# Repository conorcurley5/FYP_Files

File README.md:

# FYP Portfolio Supplementary Files

Due to the quantity of code involved in this project, all files are stored in this GitHub repository. There's almost 1GB of data here, so the portfolio would end up being significantly more than 100 pages.

# Folders

There are four folders in this project:

 - CCS Application
 - KiCAD
 - SolidWorks
 - User Interface Application

## CCS Application

This folder holds the code for the PlatformIO-based CCS software. The primary folder in here is "(Main)FYP Project - ESP", however older revisions of the software, and revisions for different platforms, are available also.

## KiCAD

This folder holds all of the PCB designs for the project, including multiple revisions of the heater, and an unused design for a motor controller board.

## SolidWorks

This folder holds all of the 3D models for the project, as well as some renders used in the portfolio.

- Assemblies holds packaged assemblies for the project. RigV2 is the version used in the portfolio.
- Renders holds the renders used in the report.
- All files holds every revision of every file in the project, but these aren't packed to go.

## User Interface Application

This folder holds the front-end application for the project, build with NextJS. There is only one version of this application. You'll need NodeJS installed to run these.

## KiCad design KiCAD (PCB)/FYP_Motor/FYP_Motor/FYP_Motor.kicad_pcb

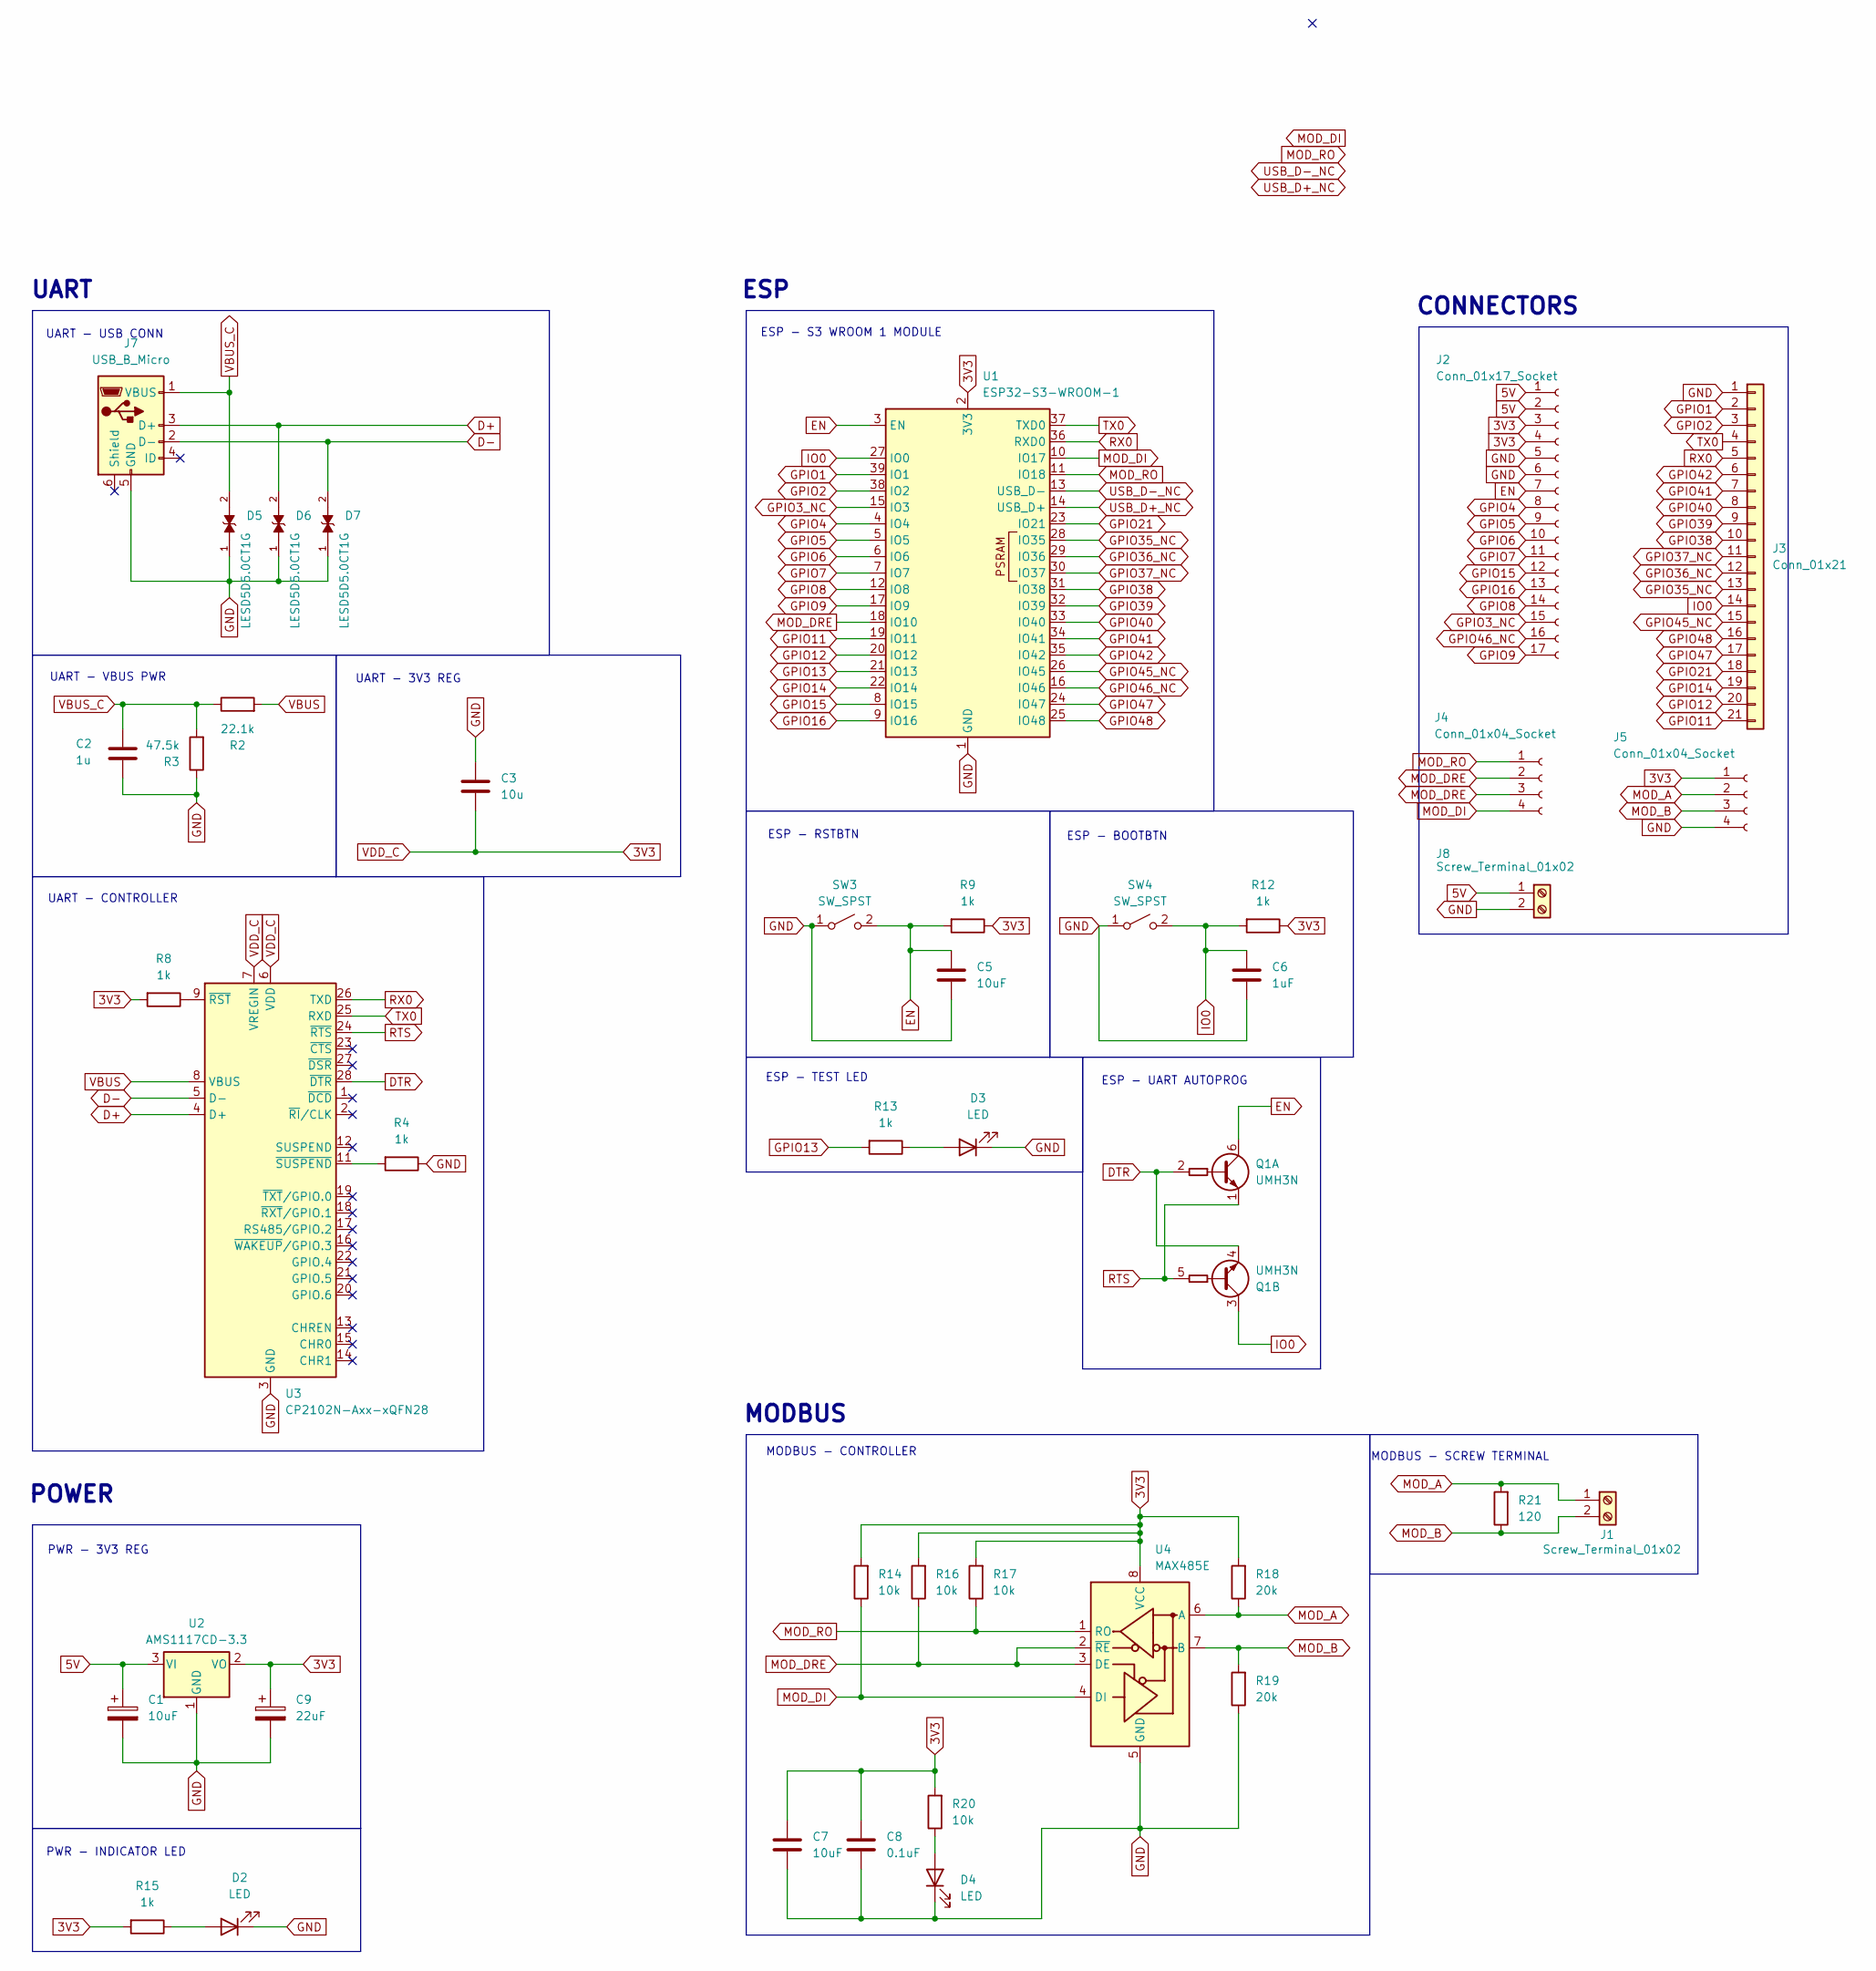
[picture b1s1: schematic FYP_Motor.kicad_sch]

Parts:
C1: 10uF; CP_EIA-3216-18_Kemet-A
C2: 1u; C_0402_1005Metric
C3: 10u; C_0603_1608Metric
C5, C7: 10uF; C_0603_1608Metric
C6: 1uF; C_0402_1005Metric
C8: 0.1uF; C_0402_1005Metric
C9: 22uF; CP_EIA-3216-18_Kemet-A
D2, D3, D4: LED; LED_0603_1608Metric
D5, D6, D7: LESD5D5.0CT1G; TVS_LESD5D5.0CT1G; PARTREV O
J1, J8: Screw_Terminal_01x02; TerminalBlock_Altech_AK300-2_P5.00mm
J2: Conn_01x17_Socket; PinSocket_1x17_P1.27mm_Vertical
J3: Conn_01x21; PinSocket_1x21_P1.27mm_Vertical
J4, J5: Conn_01x04_Socket; PinHeader_1x04_P1.27mm_Vertical
J7: USB_B_Micro; USB_Micro-B_Wuerth_629105150521
Q1: UMH3N; SOT-363_SC-70-6
R2: 22.1k; R_0603_1608Metric
R3: 47.5k; R_0603_1608Metric
R4, R8, R9, R12, R13, R15: 1k; R_0603_1608Metric
R14, R16, R17, R20: 10k; R_0603_1608Metric
R18, R19: 20k; R_0603_1608Metric
R21: 120; R_0603_1608Metric
SW3, SW4: SW_SPST; SW_SPST_B3U-1000P
U1: ESP32-S3-WROOM-1
U2: AMS1117CD-3.3; TO-252-3_TabPin2
U3: CP2102N-Axx-xQFN28; QFN-28-1EP_5x5mm_P0.5mm_EP3.35x3.35mm
U4: MAX485E; SOIC-8_3.9x4.9mm_P1.27mm

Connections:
3V3: C3.2, C7.1, C8.1, C9.1, J2.3, J2.4, J5.1, R8.2, R9.1, R12.1, R14.2, R15.2, R16.2, R17.2, R18.2, R20.2, U1.2 (3V3), U2.2 (VO), U3.6 (VDD), U3.7 (VREGIN), U4.8 (VCC)
5V: C1.1, J2.1, J2.2, J8.1, U2.3 (VI)
D+: D6.2, J7.3 (D+), U3.4 (D+)
D-: D7.2, J7.2 (D-), U3.5 (D-)
DTR: Q1.2 (B1), Q1.4 (E2), U3.28 (~DTR)
EN: C5.1, J2.7, Q1.6 (C1), R9.2, SW3.2 (B), U1.3 (EN)
GND: C1.2, C2.1, C3.1, C5.2, C6.2, C7.2, C8.2, C9.2, D2.1 (K), D3.1 (K), D4.1 (K), D5.1, D6.1, D7.1, J2.5, J2.6, J3.1, J5.4, J7.5 (GND), J8.2, R3.1, R4.1, R19.1, SW3.1 (A), SW4.1 (A), U1.1 (GND), U1.40 (GND), U1.41 (GND), U2.1 (GND), U3.3 (GND), U3.29 (GND), U4.5 (GND)
GPIO1: J3.2, U1.39 (IO1)
GPIO2: J3.3, U1.38 (IO2)
GPIO3_NC: J2.15, U1.15 (IO3)
GPIO4: J2.8, U1.4 (IO4)
GPIO5: J2.9, U1.5 (IO5)
GPIO6: J2.10, U1.6 (IO6)
GPIO7: J2.11, U1.7 (IO7)
GPIO8: J2.14, U1.12 (IO8)
GPIO9: J2.17, U1.17 (IO9)
GPIO11: J3.21, U1.19 (IO11)
GPIO12: J3.20, U1.20 (IO12)
GPIO13: R13.2, U1.21 (IO13)
GPIO14: J3.19, U1.22 (IO14)
GPIO15: J2.12, U1.8 (IO15)
GPIO16: J2.13, U1.9 (IO16)
GPIO21: J3.18, U1.23 (IO21)
GPIO35_NC: J3.13, U1.28 (IO35)
GPIO36_NC: J3.12, U1.29 (IO36)
GPIO37_NC: J3.11, U1.30 (IO37)
GPIO38: J3.10, U1.31 (IO38)
GPIO39: J3.9, U1.32 (IO39)
GPIO40: J3.8, U1.33 (IO40)
GPIO41: J3.7, U1.34 (IO41)
GPIO42: J3.6, U1.35 (IO42)
GPIO45_NC: J3.15, U1.26 (IO45)
GPIO46_NC: J2.16, U1.16 (IO46)
GPIO47: J3.17, U1.24 (IO47)
GPIO48: J3.16, U1.25 (IO48)
IO0: C6.1, J3.14, Q1.3 (C2), R12.2, SW4.2 (B), U1.27 (IO0)
MOD_A: J1.1, J5.2, R18.1, R21.2, U4.6 (A)
MOD_B: J1.2, J5.3, R19.2, R21.1, U4.7 (B)
MOD_DI: J4.4, R14.1, U1.10 (IO17), U4.4 (DI)
MOD_DRE: J4.2, J4.3, R16.1, U1.18 (IO10), U4.2 (~RE), U4.3 (DE)
MOD_RO: J4.1, R17.1, U1.11 (IO18), U4.1 (RO)
unnamed: D2.2 (A), R15.1
unnamed: D3.2 (A), R13.1
unnamed: D4.2 (A), R20.1
unnamed: R8.1, U3.9 (~RST)
unnamed: R4.2, U3.11 (~SUSPEND)
RTS: Q1.1 (E1), Q1.5 (B2), U3.24 (~RTS)
RX0: J3.5, U1.36 (RXD0), U3.26 (TXD)
TX0: J3.4, U1.37 (TXD0), U3.25 (RXD)
USB_D+_NC: U1.14 (USB_D+)
USB_D-_NC: U1.13 (USB_D-)
VBUS: R2.2, U3.8 (VBUS)
VBUS_C: C2.2, D5.2, J7.1 (VBUS), R2.1, R3.2

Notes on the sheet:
ESP - UART AUTOPROG
ESP - RSTBTN
ESP - TEST LED
UART - CONTROLLER
ESP - BOOTBTN
CONNECTORS
PWR - 3V3 REG
MODBUS - CONTROLLER
MODBUS - SCREW TERMINAL
UART - USB CONN
UART - 3V3 REG
UART
ESP - S3 WROOM 1 MODULE
ESP
POWER
MODBUS
UART - VBUS PWR
PWR - INDICATOR LED

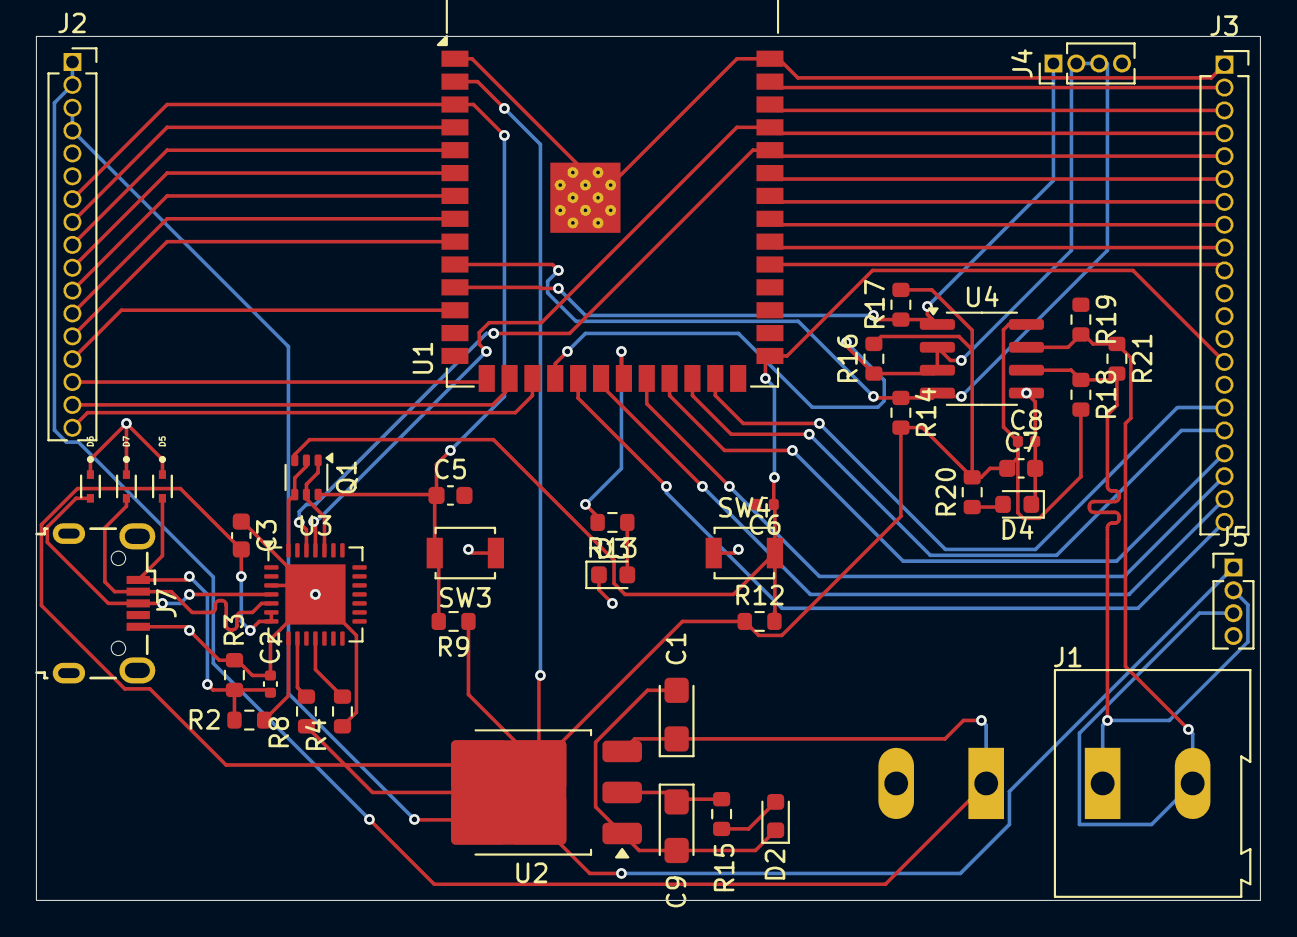
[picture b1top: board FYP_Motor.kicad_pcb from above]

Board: 2 copper layers, 68.0 x 48.0 mm, 43 parts (1 on the bottom side), 51 nets.

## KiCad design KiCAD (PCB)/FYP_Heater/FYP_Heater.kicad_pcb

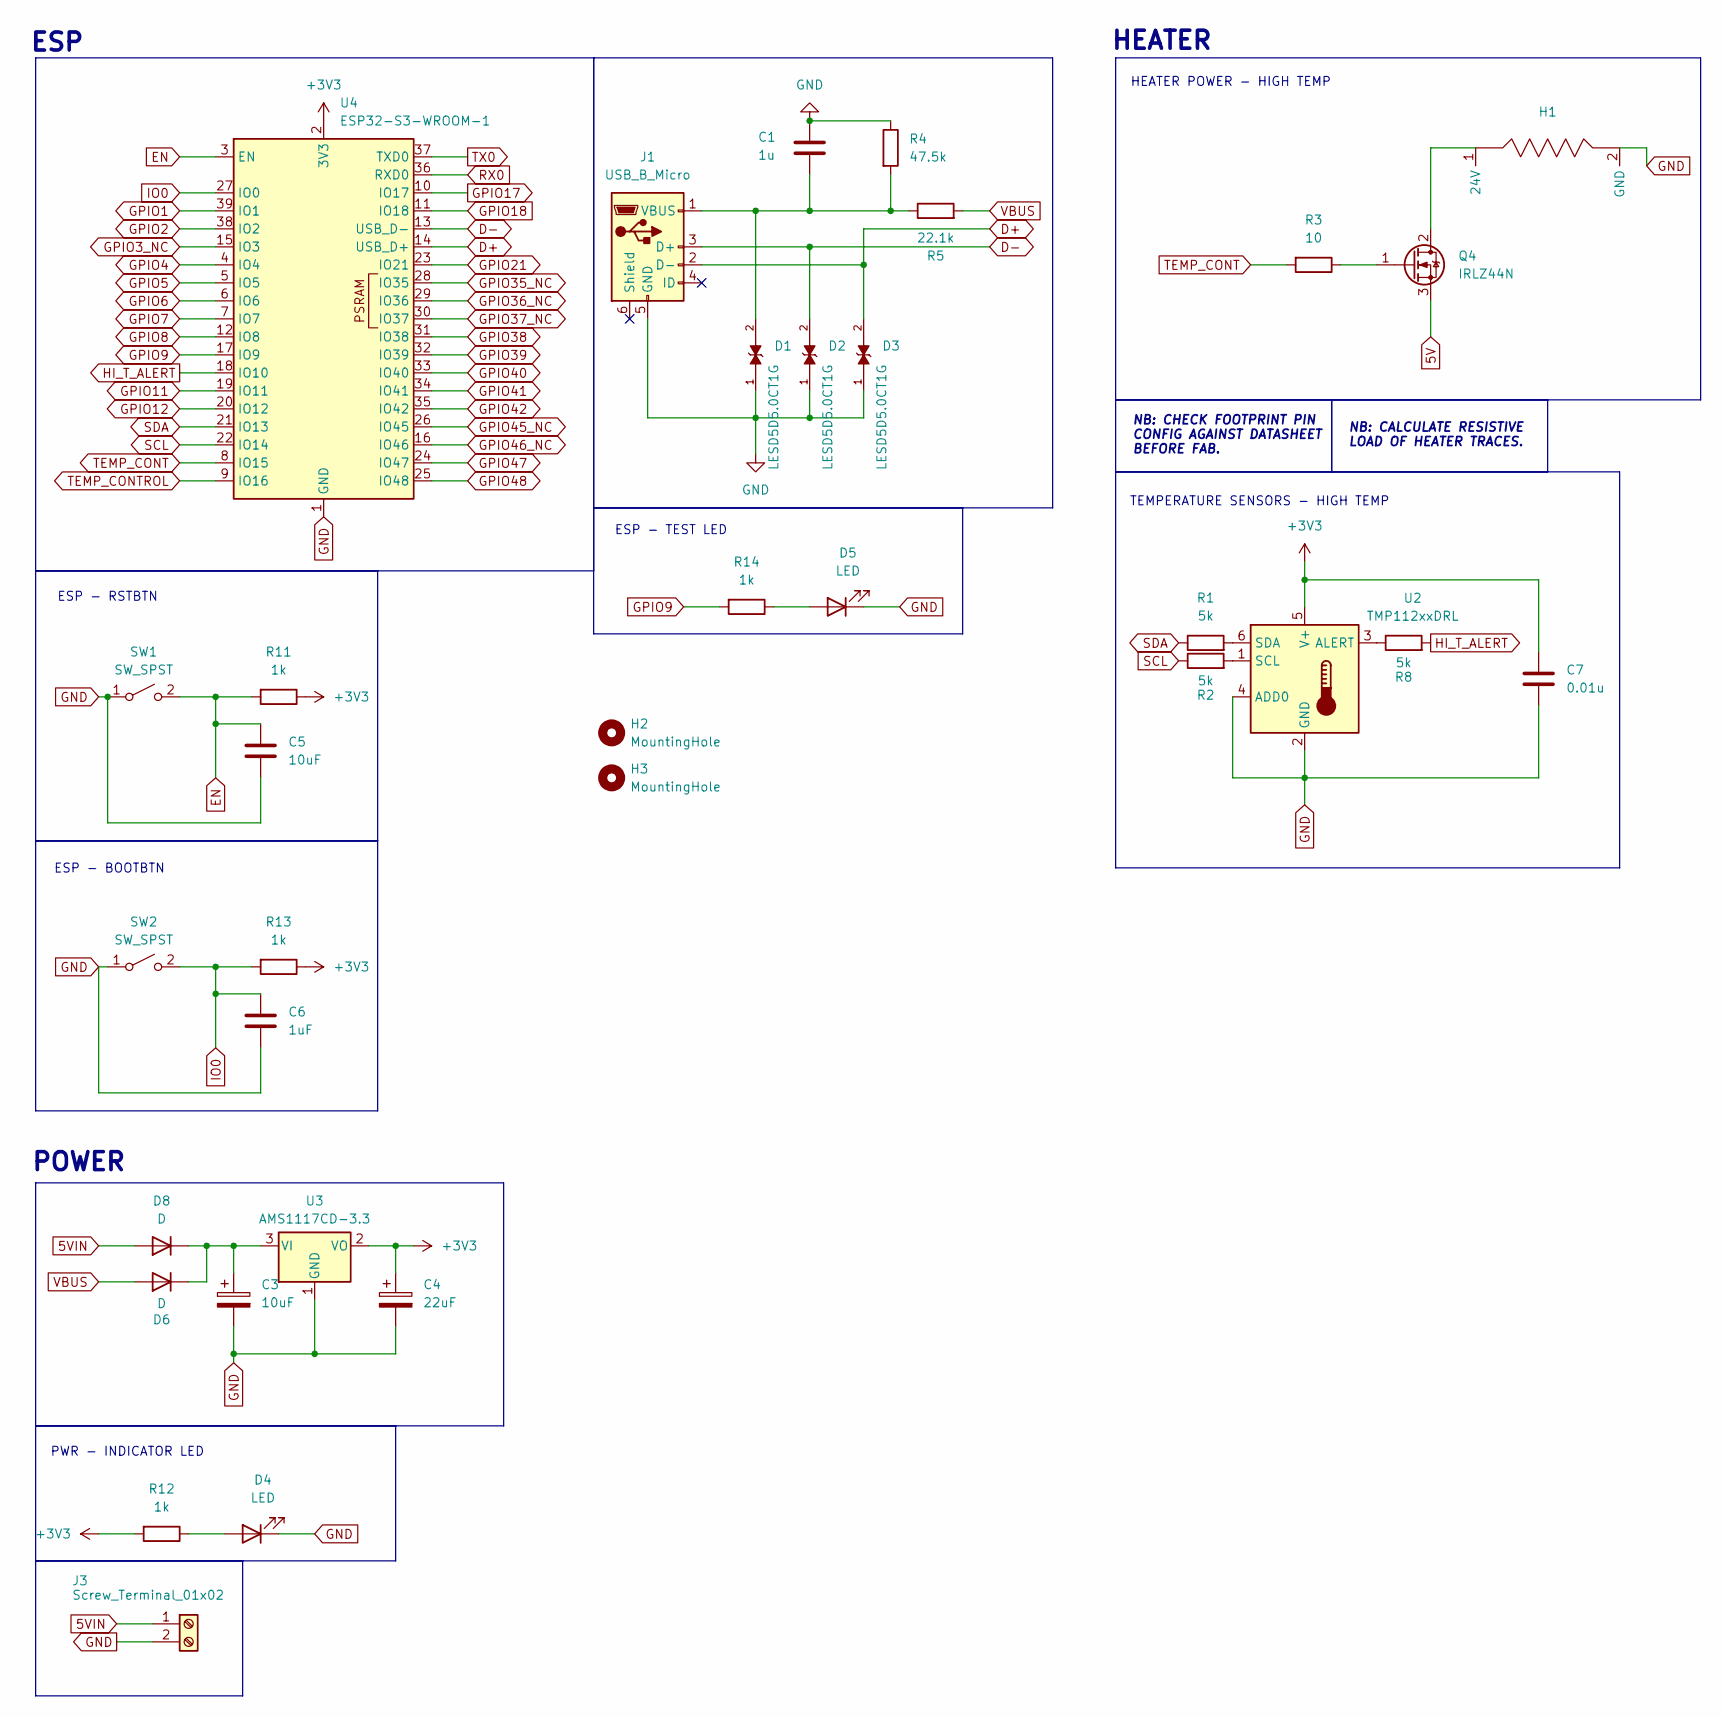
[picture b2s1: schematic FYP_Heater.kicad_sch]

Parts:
C1: 1u; C_0402_1005Metric
C3: 10uF; CP_EIA-3216-18_Kemet-A
C4: 22uF; CP_EIA-3216-18_Kemet-A
C5: 10uF; C_0603_1608Metric
C6: 1uF; C_0402_1005Metric
C7: 0.01u; C_0201_0603Metric
D1, D2, D3: LESD5D5.0CT1G; TVS_LESD5D5.0CT1G; PARTREV O
D4, D5: LED; LED_0603_1608Metric
D6, D8: D; D_SMA
H1: 24V-5A-Heater
H2, H3: MountingHole; MountingHole_3.2mm_M3
J1: USB_B_Micro; USB_Micro-B_Wuerth_629105150521
J3: Screw_Terminal_01x02; TerminalBlock_Altech_AK300-2_P5.00mm
Q4: IRLZ44N; TO-220-3_Vertical
R1, R2, R8: 5k; R_0603_1608Metric
R3: 10; R_0603_1608Metric
R4: 47.5k; R_0603_1608Metric
R5: 22.1k; R_0603_1608Metric
R11, R12, R13, R14: 1k; R_0603_1608Metric
SW1, SW2: SW_SPST; SW_SPST_B3U-1000P
U2: TMP112xxDRL; SOT-563
U3: AMS1117CD-3.3; TO-252-3_TabPin2
U4: ESP32-S3-WROOM-1

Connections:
5V: Q4.3 (S)
5VIN: D8.2 (A), J3.1
+3V3: C4.1, C7.1, R11.1, R12.2, R13.1, U2.5 (V+), U3.2 (VO), U4.2 (3V3)
D+: D3.2, J1.2 (D-), U4.14 (USB_D+)
D-: D2.2, J1.3 (D+), U4.13 (USB_D-)
EN: C5.1, R11.2, SW1.2 (B), U4.3 (EN)
GND: C1.2, C3.2, C4.2, C5.2, C6.2, C7.2, D1.1, D2.1, D3.1, D4.1 (K), D5.1 (K), H1.2 (GND), J1.5 (GND), J3.2, R4.1, SW1.1 (A), SW2.1 (A), U2.2 (GND), U2.4 (ADD0), U3.1 (GND), U4.1 (GND), U4.40 (GND), U4.41 (GND)
GPIO1: U4.39 (IO1)
GPIO2: U4.38 (IO2)
GPIO3_NC: U4.15 (IO3)
GPIO4: U4.4 (IO4)
GPIO5: U4.5 (IO5)
GPIO6: U4.6 (IO6)
GPIO7: U4.7 (IO7)
GPIO8: U4.12 (IO8)
GPIO9: R14.2, U4.17 (IO9)
GPIO11: U4.19 (IO11)
GPIO12: U4.20 (IO12)
GPIO17: U4.10 (IO17)
GPIO18: U4.11 (IO18)
GPIO21: U4.23 (IO21)
GPIO35_NC: U4.28 (IO35)
GPIO36_NC: U4.29 (IO36)
GPIO37_NC: U4.30 (IO37)
GPIO38: U4.31 (IO38)
GPIO39: U4.32 (IO39)
GPIO40: U4.33 (IO40)
GPIO41: U4.34 (IO41)
GPIO42: U4.35 (IO42)
GPIO45_NC: U4.26 (IO45)
GPIO46_NC: U4.16 (IO46)
GPIO47: U4.24 (IO47)
GPIO48: U4.25 (IO48)
HI_T_ALERT: R8.2, U4.18 (IO10)
IO0: C6.1, R13.2, SW2.2 (B), U4.27 (IO0)
unnamed: D4.2 (A), R12.1
unnamed: D5.2 (A), R14.1
unnamed: C3.1, D6.1 (K), D8.1 (K), U3.3 (VI)
unnamed: H1.1 (24V), Q4.2 (D)
unnamed: C1.1, D1.2, J1.1 (VBUS), R4.2, R5.1
unnamed: Q4.1 (G), R3.1
unnamed: R8.1, U2.3 (ALERT)
unnamed: R2.2, U2.1 (SCL)
unnamed: R1.2, U2.6 (SDA)
RX0: U4.36 (RXD0)
SCL: R2.1, U4.22 (IO14)
SDA: R1.1, U4.21 (IO13)
TEMP_CONT: R3.2, U4.8 (IO15)
TEMP_CONTROL: U4.9 (IO16)
TX0: U4.37 (TXD0)
VBUS: D6.2 (A), R5.2

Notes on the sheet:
ESP - TEST LED
PWR - INDICATOR LED
ESP - BOOTBTN
NB: CALCULATE RESISTIVE LOAD OF HEATER TRACES.
NB: CHECK FOOTPRINT PIN CONFIG AGAINST DATASHEET BEFORE FAB.
TEMPERATURE SENSORS - HIGH TEMP
ESP - RSTBTN
HEATER
ESP
POWER
HEATER POWER - HIGH TEMP

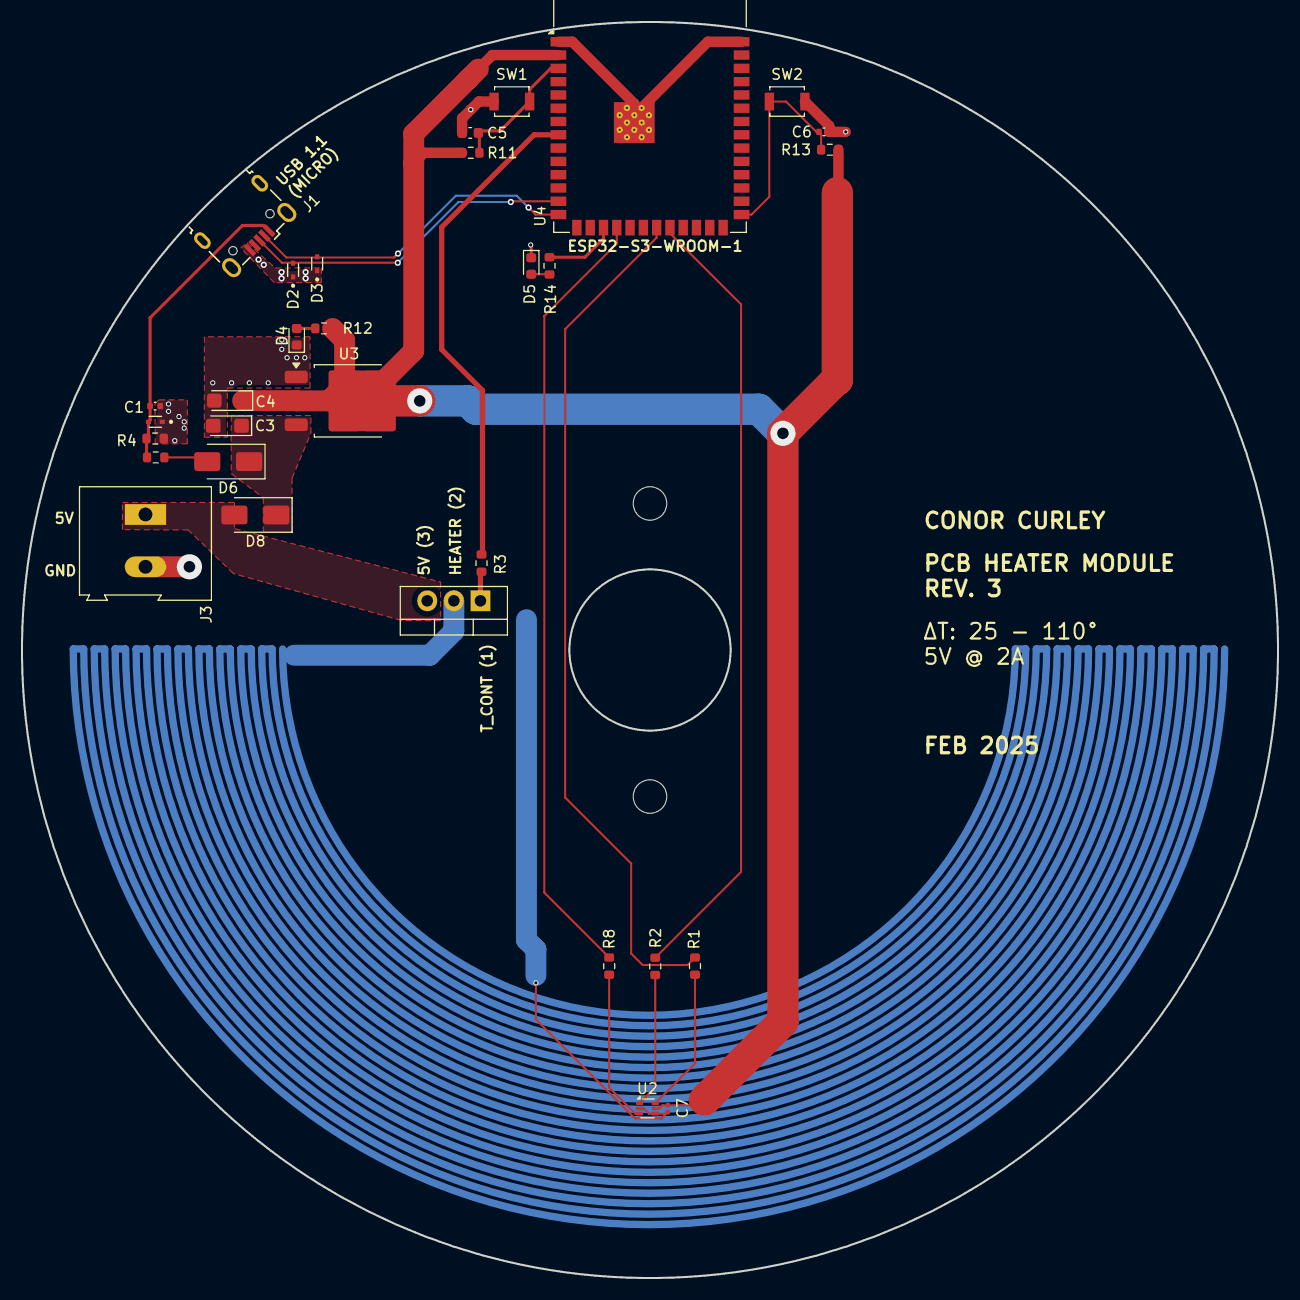
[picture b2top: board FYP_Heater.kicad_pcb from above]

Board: 2 copper layers, 120.0 x 120.0 mm, 34 parts (1 on the bottom side), 22 nets.

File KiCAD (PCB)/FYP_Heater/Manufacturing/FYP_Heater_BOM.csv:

Reference,Value,Footprint,Exclude from BOM,Exclude from Board,Exclude from Simulation,Description,Qty,JLCPCB Part #?optional?
C1,1u,Capacitor_SMD:C_0402_1005Metric,,,,Unpolarized capacitor,1,C52923
C3,10uF,Capacitor_Tantalum_SMD:CP_EIA-3216-18_Kemet-A,,,,Polarized capacitor,1,C7171
C4,22uF,Capacitor_Tantalum_SMD:CP_EIA-3216-18_Kemet-A,,,,Polarized capacitor,1,C7182
C5,10uF,Capacitor_SMD:C_0603_1608Metric,,,,Unpolarized capacitor,1,C19702
C6,1uF,Capacitor_SMD:C_0402_1005Metric,,,,Unpolarized capacitor,1,C52923
C7,0.01u,Capacitor_SMD:C_0201_0603Metric,,,,Unpolarized capacitor,1,C57112
"D1,D2,D3",LESD5D5.0CT1G,LESD5D5.0CT1G:TVS_LESD5D5.0CT1G,,,,,3,C383211
"D4,D5",LED,LED_SMD:LED_0603_1608Metric,,,,Light emitting diode,2,C2286
"D6,D8",D,Diode_SMD:D_SMA,,,,Diode,2,C511853
J1,USB_B_Micro,Connector_USB:USB_Micro-B_Wuerth_629105150521,,,,USB Micro Type B connector,1,C2894326
J3,Screw_Terminal_01x02,TerminalBlock:TerminalBlock_Altech_AK300-2_P5.00mm,,,,"Generic screw terminal, single row, 01x02, script generated (kicad-library-utils/schlib/autogen/connector/)",1,C3703
Q4,IRLZ44N,Package_TO_SOT_THT:TO-220-3_Vertical,,,,"47A Id, 55V Vds, 22mOhm Rds Single N-Channel HEXFET Power MOSFET, TO-220AB",1,C38774
"R1,R2,R8",5k,Resistor_SMD:R_0603_1608Metric,,,,Resistor,3,C2828621
R3,10,Resistor_SMD:R_0603_1608Metric,,,,Resistor,1,C22859
R4,47.5k,Resistor_SMD:R_0603_1608Metric,,,,Resistor,1,C23061
R5,22.1k,Resistor_SMD:R_0603_1608Metric,,,,Resistor,1,C137768
"R11,R12,R13,R14",1k,Resistor_SMD:R_0603_1608Metric,,,,Resistor,4,C21190
"SW1,SW2",SW_SPST,Button_Switch_SMD:SW_SPST_B3U-1000P,,,,Single Pole Single Throw (SPST) switch,2,C231329
U2,TMP112xxDRL,Package_TO_SOT_SMD:SOT-563,,,,"Digital Temperature Sensor with I2C/SMBus/Two-wire Interface, 12 bits, ±1°C, one-shot conversion, alert, nist traceable, SOT-563",1,C28927
U3,AMS1117CD-3.3,Package_TO_SOT_SMD:TO-252-3_TabPin2,,,,"1A Low Dropout regulator, positive, 3.3V fixed output, TO-252",1,C347249
U4,ESP32-S3-WROOM-1,RF_Module:ESP32-S3-WROOM-1,,,,"RF Module, ESP32-S3 SoC, Wi-Fi 802.11b/g/n, Bluetooth, BLE, 32-bit, 3.3V, onboard antenna, SMD",1,C2913204

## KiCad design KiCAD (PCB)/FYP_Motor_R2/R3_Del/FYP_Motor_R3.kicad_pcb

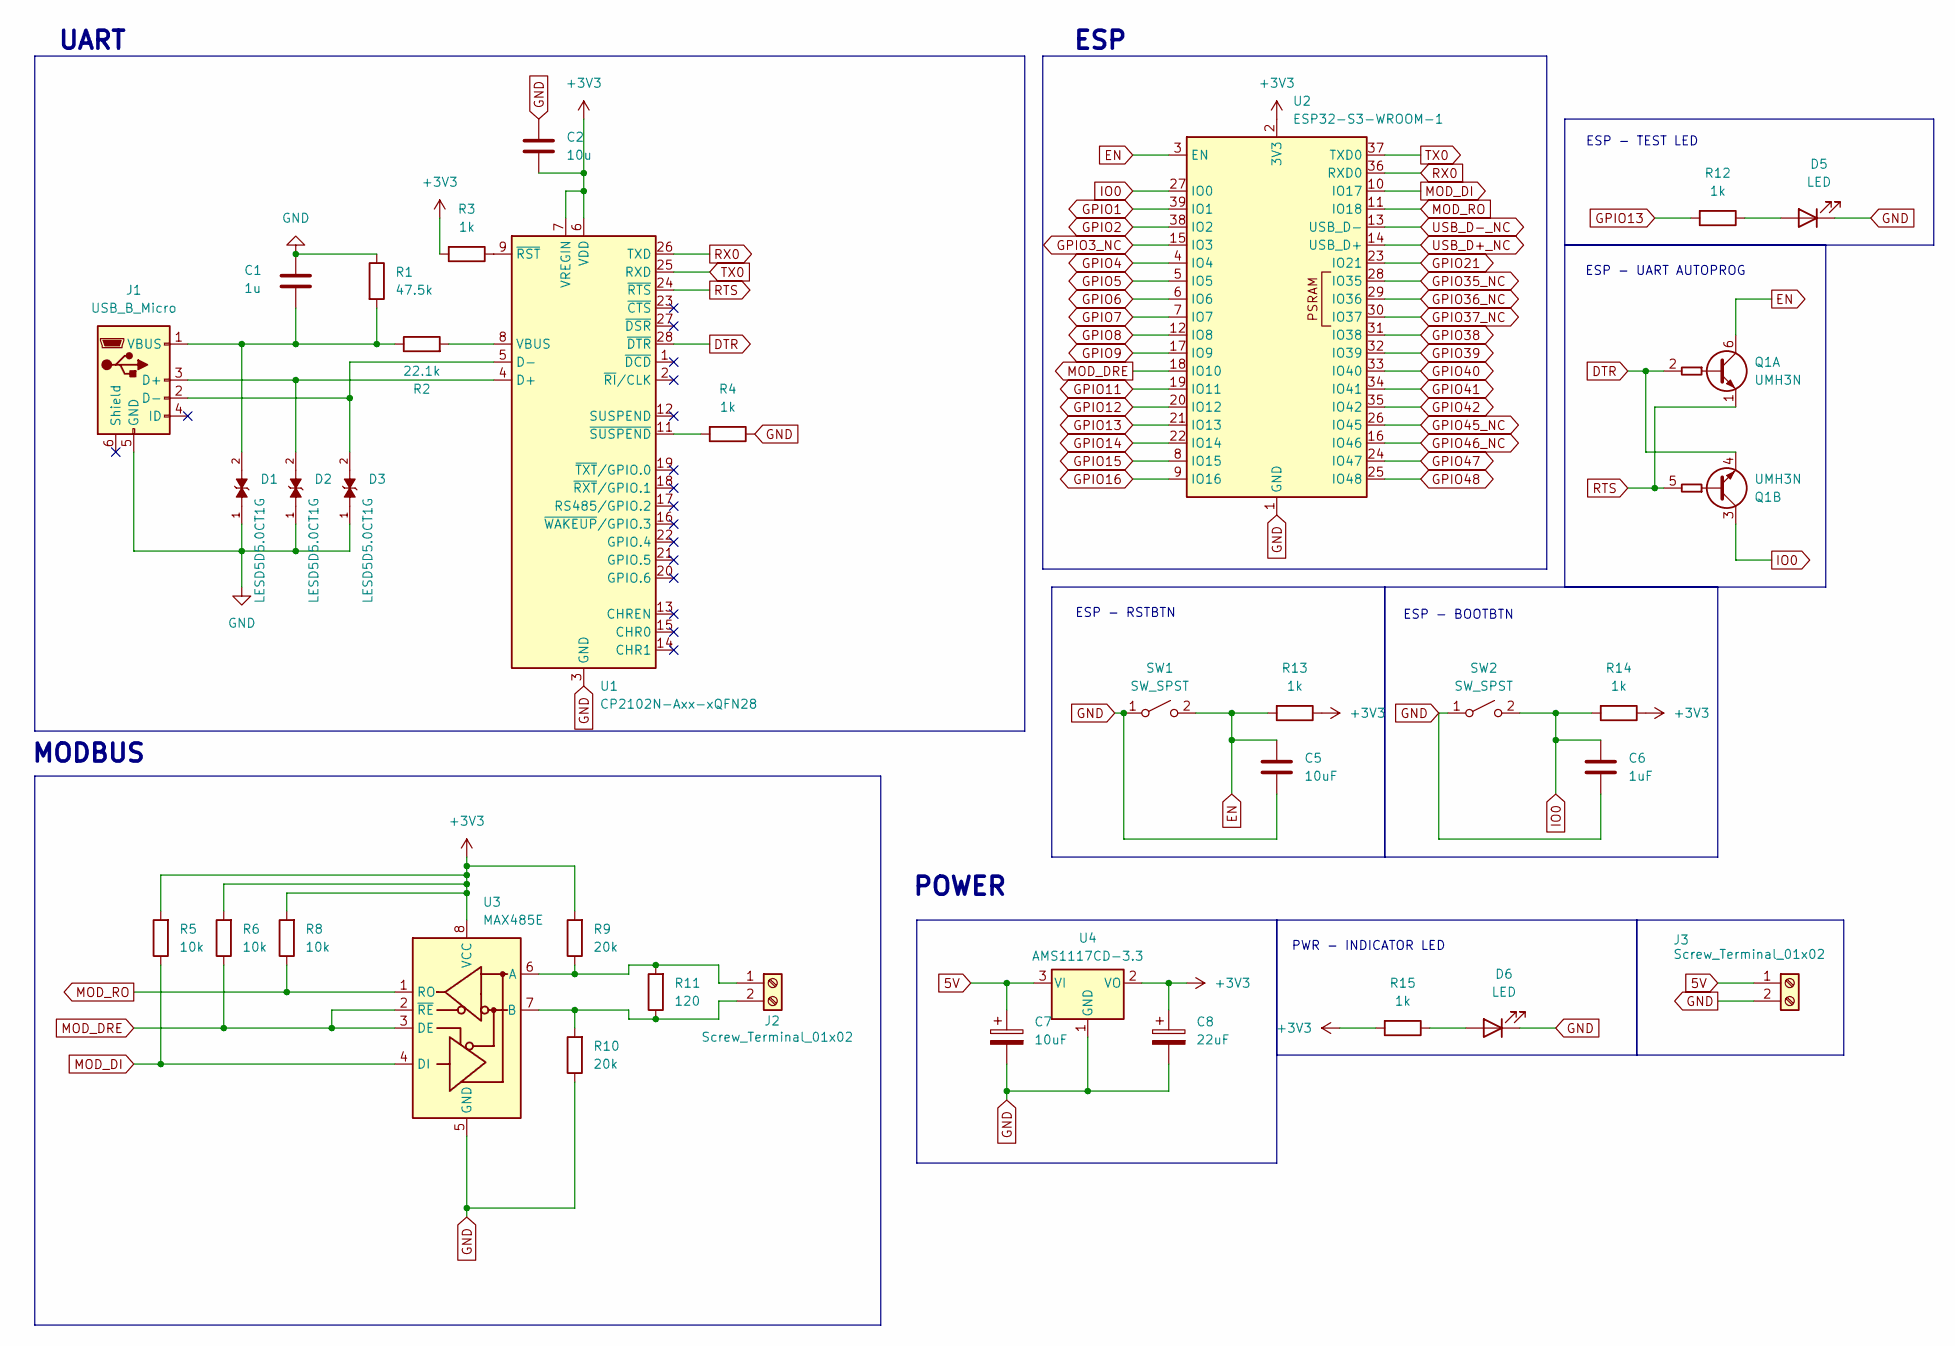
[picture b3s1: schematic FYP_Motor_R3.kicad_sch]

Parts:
C1: 1u; C_0402_1005Metric
C2: 10u; C_0603_1608Metric
C5: 10uF; C_0603_1608Metric
C6: 1uF; C_0402_1005Metric
C7: 10uF; CP_EIA-3216-18_Kemet-A
C8: 22uF; CP_EIA-3216-18_Kemet-A
D1, D2, D3: LESD5D5.0CT1G; TVS_LESD5D5.0CT1G; PARTREV O
D5, D6: LED; LED_0603_1608Metric
J1: USB_B_Micro; USB_Micro-B_Wuerth_629105150521
J2, J3: Screw_Terminal_01x02; TerminalBlock_Altech_AK300-2_P5.00mm
Q1: UMH3N; SOT-363_SC-70-6
R1: 47.5k; R_0603_1608Metric
R2: 22.1k; R_0603_1608Metric
R3, R4, R12, R13, R14, R15: 1k; R_0603_1608Metric
R5, R6, R8: 10k; R_0603_1608Metric
R9, R10: 20k; R_0603_1608Metric
R11: 120; R_0603_1608Metric
SW1, SW2: SW_SPST; SW_SPST_B3U-1000P
U1: CP2102N-Axx-xQFN28; QFN-28-1EP_5x5mm_P0.5mm_EP3.35x3.35mm
U2: ESP32-S3-WROOM-1
U3: MAX485E; SOIC-8_3.9x4.9mm_P1.27mm
U4: AMS1117CD-3.3; TO-252-3_TabPin2

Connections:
5V: C7.1, J3.1, U4.3 (VI)
+3V3: C2.1, C8.1, R3.2, R5.2, R6.2, R8.2, R9.2, R13.1, R14.1, R15.2, U1.6 (VDD), U1.7 (VREGIN), U2.2 (3V3), U3.8 (VCC), U4.2 (VO)
DTR: Q1.2 (B1), Q1.4 (E2), U1.28 (~DTR)
EN: C5.1, Q1.6 (C1), R13.2, SW1.2 (B), U2.3 (EN)
GND: C1.2, C2.2, C5.2, C6.2, C7.2, C8.2, D1.1, D2.1, D3.1, D5.1 (K), D6.1 (K), J1.5 (GND), J3.2, R1.1, R4.1, R10.1, SW1.1 (A), SW2.1 (A), U1.3 (GND), U1.29 (GND), U2.1 (GND), U2.40 (GND), U2.41 (GND), U3.5 (GND), U4.1 (GND)
GPIO1: U2.39 (IO1)
GPIO2: U2.38 (IO2)
GPIO3_NC: U2.15 (IO3)
GPIO4: U2.4 (IO4)
GPIO5: U2.5 (IO5)
GPIO6: U2.6 (IO6)
GPIO7: U2.7 (IO7)
GPIO8: U2.12 (IO8)
GPIO9: U2.17 (IO9)
GPIO11: U2.19 (IO11)
GPIO12: U2.20 (IO12)
GPIO13: R12.2, U2.21 (IO13)
GPIO14: U2.22 (IO14)
GPIO15: U2.8 (IO15)
GPIO16: U2.9 (IO16)
GPIO21: U2.23 (IO21)
GPIO35_NC: U2.28 (IO35)
GPIO36_NC: U2.29 (IO36)
GPIO37_NC: U2.30 (IO37)
GPIO38: U2.31 (IO38)
GPIO39: U2.32 (IO39)
GPIO40: U2.33 (IO40)
GPIO41: U2.34 (IO41)
GPIO42: U2.35 (IO42)
GPIO45_NC: U2.26 (IO45)
GPIO46_NC: U2.16 (IO46)
GPIO47: U2.24 (IO47)
GPIO48: U2.25 (IO48)
IO0: C6.1, Q1.3 (C2), R14.2, SW2.2 (B), U2.27 (IO0)
MOD_DI: R5.1, U2.10 (IO17), U3.4 (DI)
MOD_DRE: R6.1, U2.18 (IO10), U3.2 (~RE), U3.3 (DE)
MOD_RO: R8.1, U2.11 (IO18), U3.1 (RO)
unnamed: D5.2 (A), R12.1
unnamed: D6.2 (A), R15.1
unnamed: D2.2, J1.3 (D+), U1.4 (D+)
unnamed: D3.2, J1.2 (D-), U1.5 (D-)
unnamed: C1.1, D1.2, J1.1 (VBUS), R1.2, R2.1
unnamed: J2.1, R9.1, R11.2, U3.6 (A)
unnamed: J2.2, R10.2, R11.1, U3.7 (B)
unnamed: R2.2, U1.8 (VBUS)
unnamed: R3.1, U1.9 (~RST)
unnamed: R4.2, U1.11 (~SUSPEND)
RTS: Q1.1 (E1), Q1.5 (B2), U1.24 (~RTS)
RX0: U1.26 (TXD), U2.36 (RXD0)
TX0: U1.25 (RXD), U2.37 (TXD0)
USB_D+_NC: U2.14 (USB_D+)
USB_D-_NC: U2.13 (USB_D-)

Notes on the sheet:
UART
ESP - UART AUTOPROG
ESP - TEST LED
POWER
ESP - RSTBTN
PWR - INDICATOR LED
ESP
MODBUS
ESP - BOOTBTN

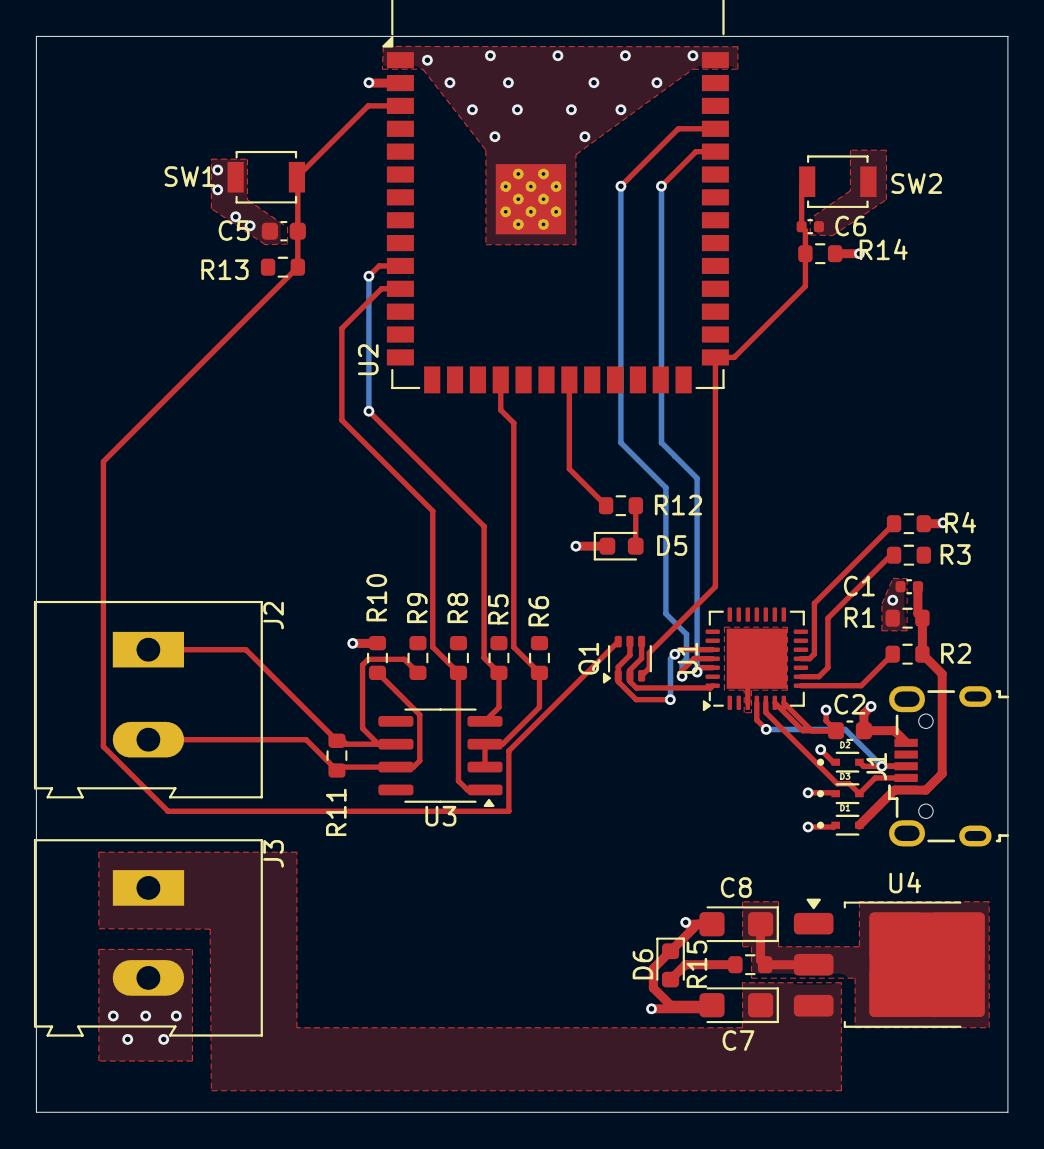
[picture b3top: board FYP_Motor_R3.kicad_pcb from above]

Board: 4 copper layers, 54.0 x 59.8 mm, 35 parts (0 on the bottom side), 23 nets.

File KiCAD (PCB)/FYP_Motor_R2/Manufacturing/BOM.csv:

"Reference","Value","Datasheet","Footprint","Qty","DNP"
"C1","1u","~","Capacitor_SMD:C_0402_1005Metric","1",""
"C2","10u","~","Capacitor_SMD:C_0603_1608Metric","1",""
"C5,C7","10uF","~","-- mixed values --","2",""
"C6","1uF","~","Capacitor_SMD:C_0402_1005Metric","1",""
"C8","22uF","~","Capacitor_Tantalum_SMD:CP_EIA-3216-18_Kemet-A","1",""
"D1,D2,D3","LESD5D5.0CT1G","","LESD5D5.0CT1G:TVS_LESD5D5.0CT1G","3",""
"D5,D6","LED","~","LED_SMD:LED_0603_1608Metric","2",""
"J1","USB_B_Micro","~","Connector_USB:USB_Micro-B_Wuerth_629105150521","1",""
"J2,J3","Screw_Terminal_01x02","~","TerminalBlock:TerminalBlock_Altech_AK300-2_P5.00mm","2",""
"Q1","UMH3N","http://rohmfs.rohm.com/en/products/databook/datasheet/discre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","Package_TO_SOT_SMD:SOT-363_SC-70-6","1",""
"R1","47.5k","~","Resistor_SMD:R_0603_1608Metric","1",""
"R2","22.1k","~","Resistor_SMD:R_0603_1608Metric","1",""
"R3,R4,R12,R13,R14,R15","1k","~","Resistor_SMD:R_0603_1608Metric","6",""
"R5,R6,R8","10k","~","Resistor_SMD:R_0603_1608Metric","3",""
"R9,R10","20k","~","Resistor_SMD:R_0603_1608Metric","2",""
"R11","120","~","Resistor_SMD:R_0603_1608Metric","1",""
"SW1,SW2","SW_SPST","~","Button_Switch_SMD:SW_SPST_B3U-1000P","2",""
"U1","CP2102N-Axx-xQFN28","https://www.silabs.com/documents/public/data-sheets/cp2102n-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","Package_DFN_QFN:QFN-28-1EP_5x5mm_P0.5mm_EP3.35x3.35mm","1",""
"U2","ESP32-S3-WROOM-1","https://www.espressif.com/sites/default/files/documentation/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","RF_Module:ESP32-S3-WROOM-1","1",""
"U3","MAX485E","https://datasheets.maximintegrated.com/en/ds/MAX1487E-MAX491E.pdf","Package_SO:SOIC-8_3.9x4.9mm_P1.27mm","1",""
"U4","AMS1117CD-3.3","http://www.advanced-monolithic.com/pdf/ds1117.pdf","Package_TO_SOT_SMD:TO-252-3_TabPin2","1",""
